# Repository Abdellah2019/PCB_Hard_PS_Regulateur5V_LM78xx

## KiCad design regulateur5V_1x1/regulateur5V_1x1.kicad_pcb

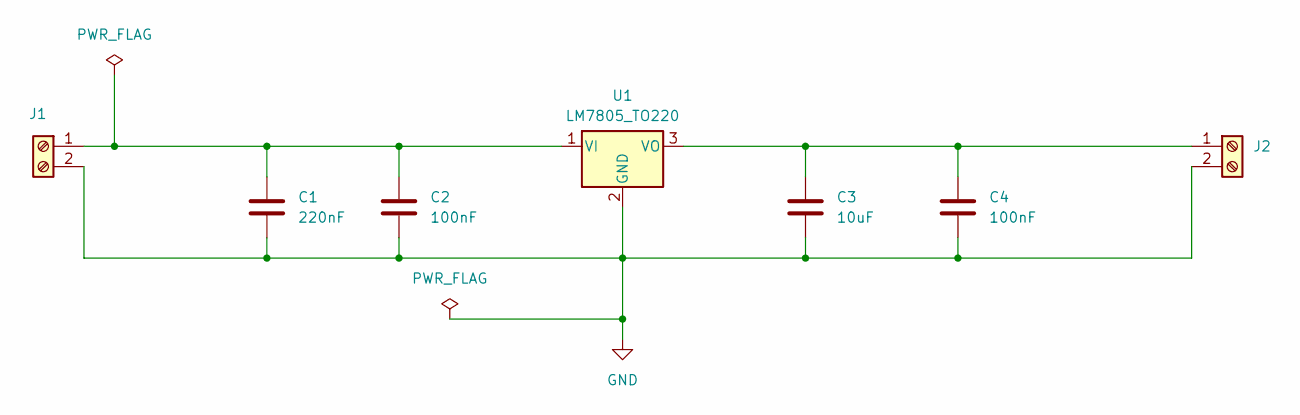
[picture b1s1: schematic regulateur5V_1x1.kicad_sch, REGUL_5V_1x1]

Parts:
C1: 220nF; C_Disc_D5.0mm_W2.5mm_P5.00mm
C2, C4: 100nF; C_Disc_D5.0mm_W2.5mm_P5.00mm
C3: 10uF; CP_Radial_D5.0mm_P2.00mm
J1, J2: Screw_Terminal_01x02; TerminalBlock_MaiXu_MX126-5.0-02P_1x02_P5.00mm
U1: LM7805_TO220; TO-220-3_Vertical

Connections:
GND: C1.2, C2.2, C3.2, C4.2, J1.2, J2.2, U1.2 (GND)
unnamed: C1.1, C2.1, J1.1, U1.1 (VI)
unnamed: C3.1, C4.1, J2.1, U1.3 (VO)

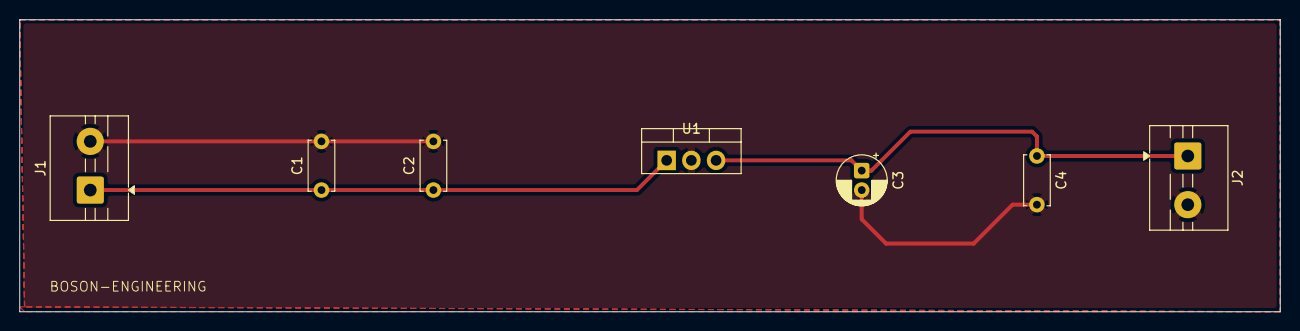
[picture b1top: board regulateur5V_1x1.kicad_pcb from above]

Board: 2 copper layers, 129.5 x 30.0 mm, 7 parts (0 on the bottom side), 3 nets.
